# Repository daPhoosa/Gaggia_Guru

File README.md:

# Gaggia Guru

ESP32-WROOM-32U control system for a converted Gaggia Classic Pro espresso machine.
PlatformIO / Arduino firmware with:

- **Wi-Fi manager** – joins a saved network; if none or it fails, starts a setup AP
  (`GaggiaGuru-Setup-XXXXXX`) with a captive portal so you can enter credentials from a phone.
  Credentials are kept in NVS and survive firmware updates.
- **OTA updates, two ways**
  - **ArduinoOTA / espota** – `pio run -e esp32-ota -t upload` from your PC.
  - **Browser upload** – Update tab on the dashboard, or the always-available
    fallback page at `/update` (works even if the filesystem is empty).
- **Async web server** serving a dashboard from LittleFS (`data/`) with live status
  over WebSocket (uptime, heap, RSSI, flash/FS usage, boot partition…).
- **mDNS** – `http://gaggia-guru.local`

> The **-32U** has no PCB antenna — connect an external 2.4 GHz antenna to the u.FL
> connector before powering up Wi-Fi.

## Layout

```
IO_design.md          pin assignments, wiring and signal conditioning (hardware reference)
docs/design_guide.md  dashboard color & design guide (live: follow it for every UI change, keep it updated)
PCB/                  KiCad 10 carrier-board schematic, project symbols and ESP32U footprint
PCB/RelayBoard/       KiCad 10 relay board (lamp relays + valve SSR), shares the PCB/ libraries
platformio.ini        build envs: esp32-serial (USB), esp32-ota (Wi-Fi), native (tests)
partitions.csv        4MB: 2 × 1.5MB OTA app slots, 896KB LittleFS, coredump
include/secrets.h     passwords, optional Wi-Fi creds (git-ignored; copy from secrets.example.h)  ← edit first
include/config.h      hostname, AP name, ports, timings
include/machine_config.h  setpoint/PID defaults, safety limits, control timing
include/io_pins.h     every GPIO: '#define PIN_X n // Name | Type | notes'
scripts/gen_io_pins.py  pre-build: io_pins.h comments → include/io_pins_table.gen.h
scripts/ota_auth.py   esp32-ota upload: takes the OTA password from secrets.h
src/main.cpp          setup/loop; loads forced OFF first, machine control started before Wi-Fi
src/machine.*         control task (own FreeRTOS task + watchdog): pin I/O, logging, status publishing
src/machine_logic.*   state machine, heater/pump PID, safety faults (hardware-free, unit-tested)
src/sensors.*         MAX31855K thermocouple, XDB401 pressure sensor via ADS1115 (pin / I2C I/O)
src/sensor_math.*     MAX31855 frame decoding, voltage -> bar (hardware-free, unit-tested)
src/pump.*            RobotDyn dimmer: zero-cross ISR, full-cycle pulse-skip modulation
src/settings.*        user settings (setpoints, PID gains) in NVS
src/settings_schema.* settings field table, defaults, range checks (hardware-free, unit-tested)
src/pid.h             PID controller
src/wifi_manager.*    STA connect, fallback AP, captive DNS, scan, NVS creds
src/ota.*             ArduinoOTA
src/web_server.*      HTTP routes, JSON API, WebSocket, browser OTA
src/io_status.*       read-only pin sampling for /api/io
src/cpu_load.*        per-core CPU load estimate (idle-task loop counting) for the Device status card
test/                 PC unit tests (pio test -e native), see test/README.md
data/                 web UI → LittleFS: index.html (dashboard), settings.html, wifi.html, test.html,
                      update.html, io.html, shared style.css + app.js, fonts/Inter.woff2
                      (styled per docs/design_guide.md)
```

## First flash (USB)

1. Create your secrets file and set real passwords in it (`OTA_PASSWORD`, `ADMIN_PASSWORD`,
   `AP_PASSWORD`, optionally `DEFAULT_WIFI_SSID` / `DEFAULT_WIFI_PASS`):
   ```sh
   cp include/secrets.example.h include/secrets.h
   ```
   `include/secrets.h` is git-ignored; the build stops with an error if it is missing.
   The Wi-Fi upload reads `OTA_PASSWORD` from it, so there is nothing to keep in sync.
2. Flash firmware and the dashboard filesystem:
   ```sh
   pio run -e esp32-serial -t upload
   pio run -e esp32-serial -t uploadfs
   pio device monitor
   ```
3. If no Wi-Fi is configured, join `GaggiaGuru-Setup-XXXXXX` (password `AP_PASSWORD`),
   browse to `http://192.168.4.1`, open **Wi-Fi**, pick a network, Save. The device reboots
   onto your network.

## Unit tests (PC, no hardware)

```sh
pio test -e native
```
Runs on the PC with the host compiler (g++ or clang). Covers the control logic and every
software safety fault, sensor decoding, settings validation and the PID. See
[test/README.md](test/README.md). Run it after changing anything in `machine_logic`,
`sensor_math`, `settings_schema` or `pid.h`.

## Updating over Wi-Fi

```sh
pio run -e esp32-ota -t upload      # firmware
pio run -e esp32-ota -t uploadfs    # dashboard files
```
If `gaggia-guru.local` doesn't resolve, set `upload_port` in `platformio.ini` to the IP.
The OTA password comes from `OTA_PASSWORD` in `include/secrets.h`; the environment variable
`GAGGIA_OTA_PASS` overrides it (e.g. when the device still has an older password).

If a filesystem upload fails part-way, the device mounts LittleFS again. If the partition was
already partly overwritten, `/` serves the built-in Wi-Fi setup page instead of the dashboard;
use its **Firmware update** link (or `uploadfs`) to upload `littlefs.bin` again.

Or from the browser: **Update** tab → choose `.pio/build/esp32-serial/firmware.bin`
(or `littlefs.bin` from `pio run -t buildfs`) → Upload. Login is `ADMIN_USER` / `ADMIN_PASSWORD`.

Bump `-DFW_VERSION` in `platformio.ini` to see the new version on the dashboard.

## HTTP API

| Method | Path                           | Auth*  | Description                          |
|--------|--------------------------------|--------|--------------------------------------|
| GET    | `/api/status`                  | –      | Device status JSON (incl. CPU load estimate, control tick timing) |
| WS     | `/ws`                          | –      | Status JSON pushed every 2 s         |
| GET    | `/api/machine`                 | –      | Machine state, temperature, pressure, outputs, fault |
| WS     | `/ws` (`"type":"machine"`)     | –      | Machine JSON pushed every 0.5 s      |
| GET    | `/api/settings`                | –      | Settings values, defaults and limits |
| POST   | `/api/settings` (any of the setting keys) | admin | Validate, apply and save settings |
| POST   | `/api/settings/reset`          | admin  | Restore default settings             |
| GET    | `/api/io`                      | –      | Pin names/types (from io_pins.h) + live state |
| GET    | `/test.html` (or `/test`)      | admin  | Output test page (manual heater / pump / valve / lights) |
| POST   | `/api/test` (`action=start`, `update`, `stop`) | admin | Start, drive (and keep alive) or stop the output test |
| GET    | `/api/wifi/scan`               | –      | Nearby networks (async; poll)        |
| POST   | `/api/wifi` (`ssid`, `pass`)   | admin† | Save credentials and reboot          |
| POST   | `/api/wifi/forget`             | admin  | Clear credentials and reboot         |
| POST   | `/api/reboot`                  | admin  | Reboot                               |
| POST   | `/api/update?target=firmware\|fs` | admin | Multipart `.bin` upload (one file), reboots on success; `409` while another update (browser or ArduinoOTA) is running |
| GET    | `/update`                      | admin  | Minimal fallback upload page         |

\* HTTP Basic auth. † Open while in setup-AP mode so first-time provisioning works.

Every POST must also carry the header `X-Guru: 1`, or an `Origin` header equal to the
device's own address; anything else gets `403`. This stops other web pages open in the
same browser from changing settings (cross-site request forgery). The dashboard pages add the
header automatically. The address used must also be one of the device's own names: its IP
address, `gaggia-guru`, or `gaggia-guru` followed by `.local`, `.lan`, `.home`, `.home.arpa`,
`.localdomain` or `.internal`. This blocks DNS rebinding, where another website's name is
pointed at the machine. POSTs sent to any other name, including through a reverse proxy, get
`403`. From a script:

```sh
curl -u admin:PASSWORD -H 'X-Guru: 1' -d coffeeTempC=93 http://gaggia-guru.local/api/settings
```

The server sends no CORS headers, so other sites can't read the API either.

## IO pin map

`include/io_pins.h` lists every usable GPIO of the ESP32-WROOM-32U in 38-pin board order.
Each active line must be:

```c
#define PIN_RELAY_1   4   // RELAY_1 | Digital | drives K1 via Q1
```

- **Type** is one of `Analog`, `Digital`, `Communications`, `Unused`.
- Lines starting with `//` are ignored (flash pins GPIO6–11, and GPIO37/38 which the module lacks).
- `scripts/gen_io_pins.py` parses the comments on every build and fails the build with a
  clear message on a bad type, duplicate GPIO, flash pin or missing comment.
- The dashboard's **IO Status** page shows each pin's name, type, mode (IN/OUT/PERIPH/ANALOG),
  pull-up/down and level (HIGH/LOW), refreshed every second. Reading is non-invasive and the
  page never touches the ADC. Brew pressure is read by the ADS1115 over I²C, so it is shown
  on the dashboard, not here.
  ADC2 pins can't be read while Wi-Fi is on — use ADC1 (GPIO32–39) for analog inputs.

## Machine operation

| Coffee | Steam | State       | Boiler target (thermocouple) | Pump        | Valve  |
|--------|-------|-------------|------------------------------|-------------|--------|
| off    | off   | `IDLE`      | coffee + offset (93 + 7 = 100 °C) | off    | closed |
| on     | off   | `BREWING`   | coffee + offset              | PID to brew pressure (6 bar) | open |
| off    | on    | `STEAM`     | steam (145 °C)               | off         | closed |
| on     | on    | `HOT_WATER` | steam                        | 100 %       | closed |

- **Output test (`TEST`):** the admin-only **Output test** page (linked from IO Status)
  switches the heater, pump (with a duty cycle, default 100 %), valve and both lights by
  hand, and shows the switches, thermocouple, pressure and mains frequency. It starts only
  from `IDLE` with both switches off and ends on Stop, either switch turning on, a fault, a
  firmware update, or 5 s without a keep-alive from the page (it sends one every second;
  closing the page stops it at once). All safety faults stay active; the manual heater is
  held off above 150 °C (2 °C hysteresis) and the pump stops after 120 s until toggled off
  and on. Leaving the test with the Coffee switch on does not start a shot: it must be cycled.
- **Brew Temp Offset** (default 7 °C, range -10 to 20 °C): how much hotter the boiler
  thermocouple reads than the water at the portafilter. The Coffee setting (default 93 °C) is
  the water temperature; in coffee mode the heater PID aims for Coffee + offset and the
  dashboard shows thermocouple − offset, so the reading compares directly with the target.
  While brewing, the PID aims `BREW_TEMP_BIAS_C` (1 °C, machine_config.h) higher still to
  make up for the incoming cold water; the shown target and ready light don't change.
  Steam and hot water ignore the offset. Safety checks always use the thermocouple; the
  dashboard's Thermocouple row shows the raw reading and target.

- **Lights:** the active mode's light comes on once the temperature is within ± the **Ready
  band** of its target, then stays on (overshoot included) until it drops more than the band
  below the target (setting, default 3 °C, range 0.5 to 10 °C; one band for both lights).
  Switching from steam to coffee, the Coffee light waits for the boiler to cool into the band.
  Both blink on a fault.
- **Coffee switch arming:** if the Coffee switch is on at power-up (or after an update),
  it is ignored until turned off and on again. The pump also stops after 120 s of
  continuous running and needs the same off/on cycle.
- **Faults** (latched until power cycle, everything off): thermocouple fault, boiler
  above 155 °C, boiler not heating at full power for 120 s (high-limit tripped, fuse,
  element or loose probe), no zero-cross signal while pumping, pressure sensor out of
  range while brewing. The dashboard shows the cause.
- Firmware updates and reboots switch all loads off first.
- Settings (temperatures, pressure, PID gains) are on the dashboard **Settings** page.

## Adding your own features

- Machine behaviour lives in `src/machine.cpp` (`tick()` runs every 50 ms).
- Add fields to `statusJson()` in `src/web_server.cpp` and render them in `data/app.js`
  — they're pushed to the dashboard automatically.
- Add routes in `WebUi::begin()`.

## Notes

- Basic auth over plain HTTP is not encrypted; keep the device on a trusted network.
- `STATUS_LED_PIN` defaults to GPIO2 (common on dev boards); set `-1` if your board differs.
- Flash size: WROOM-32U modules come in 4/8/16MB. This project assumes 4MB; for larger
  modules, change `board_build.flash_size` and enlarge the partitions.

## Troubleshooting

- **Android Chrome can't open the dashboard (Firefox can):** newer Android versions require apps
  to have permission to reach local-network devices. Settings → Apps → Chrome → Permissions →
  **Nearby devices** (a.k.a. *Local network*) → Allow.
- **`pio run -e esp32-ota -t upload` stops at "No response from device":** the ESP32 connects
  back to the PC on a TCP host port (3233–3240, picked per upload by `scripts/espota_port.py`). Allow the range in the PC firewall, e.g.
  `sudo ufw allow from 192.168.1.0/24 to any port 3233:3240 proto tcp`.

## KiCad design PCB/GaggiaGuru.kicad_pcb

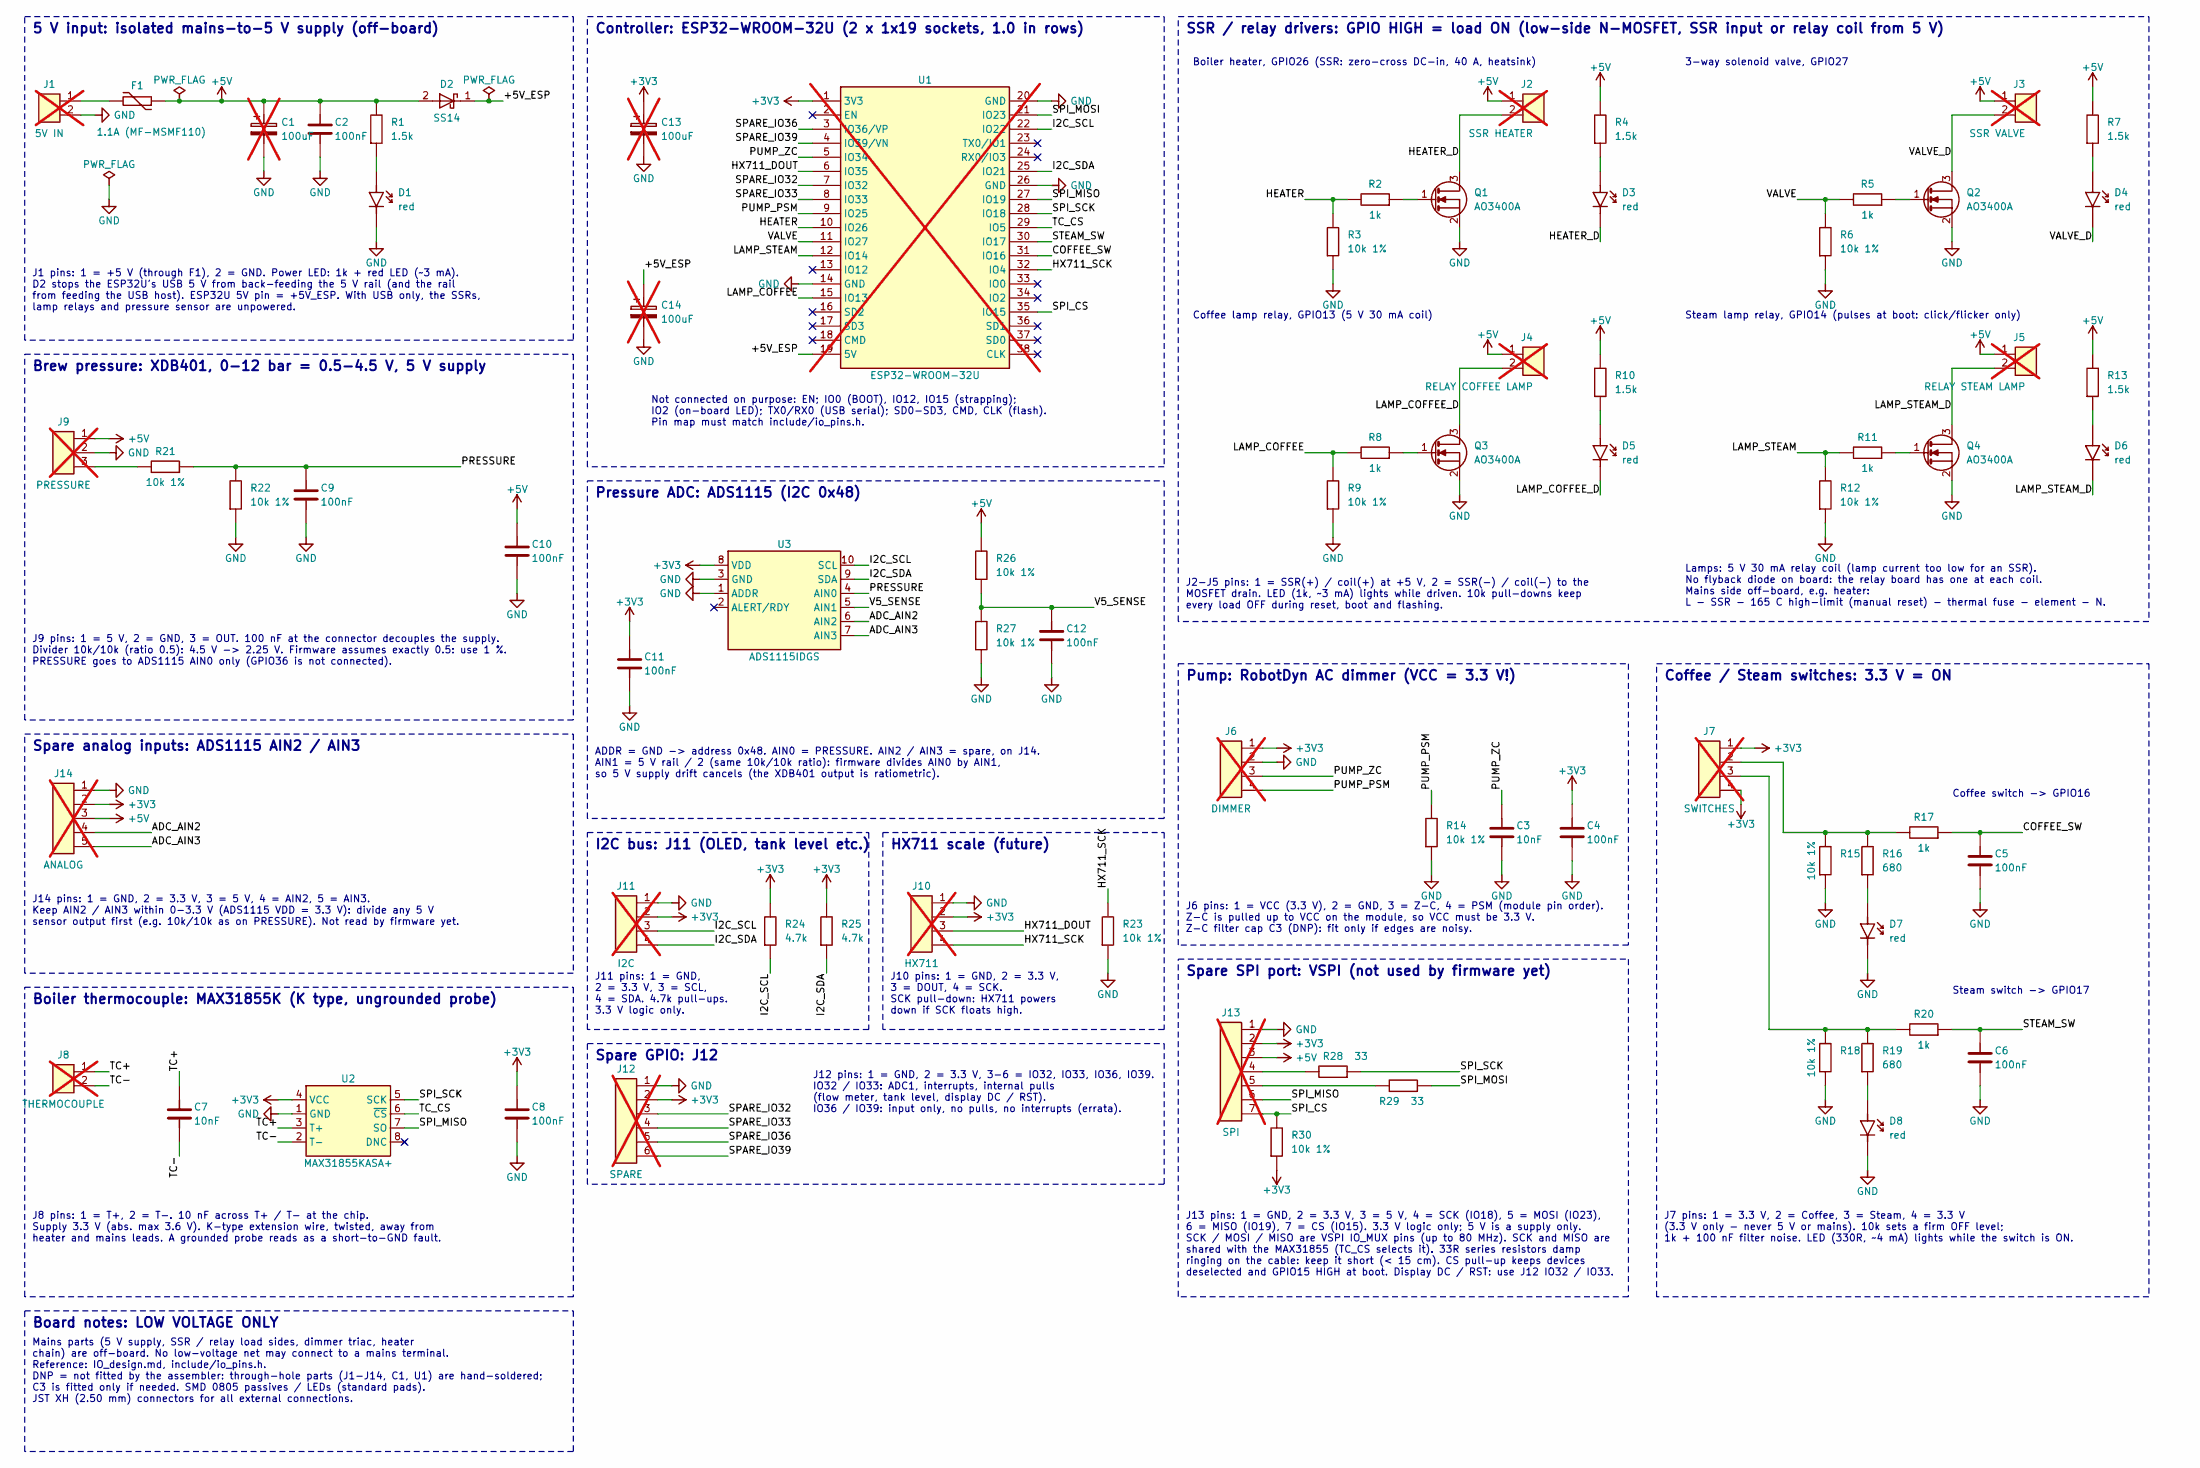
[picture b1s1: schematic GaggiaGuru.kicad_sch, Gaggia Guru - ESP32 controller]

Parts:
C1, C13, C14: 100uF; CP_Radial_D6.3mm_P2.50mm; Rating 10 V min, low ESR, radial THT; not fitted
C2, C4, C5, C6, C8, C9, C10, C11, C12: 100nF; C_0805_2012Metric
C3, C7: 10nF; C_0805_2012Metric
D1, D3, D4, D5, D6, D7, D8: red; LED_0805_2012Metric
D2: SS14; D_SMA
F1: 1.1A (MF-MSMF110); Fuse_1812_4532Metric
J1: 5V IN; JST_XH_B2B-XH-A_1x02_P2.50mm_Vertical; not fitted
J2: SSR HEATER; JST_XH_B2B-XH-A_1x02_P2.50mm_Vertical; not fitted
J3: SSR VALVE; JST_XH_B2B-XH-A_1x02_P2.50mm_Vertical; not fitted
J4: RELAY COFFEE LAMP; JST_XH_B2B-XH-A_1x02_P2.50mm_Vertical; not fitted
J5: RELAY STEAM LAMP; JST_XH_B2B-XH-A_1x02_P2.50mm_Vertical; not fitted
J6: DIMMER; JST_XH_B4B-XH-A_1x04_P2.50mm_Vertical; not fitted
J7: SWITCHES; JST_XH_B4B-XH-A_1x04_P2.50mm_Vertical; not fitted
J8: THERMOCOUPLE; JST_XH_B2B-XH-A_1x02_P2.50mm_Vertical; not fitted
J9: PRESSURE; JST_XH_B3B-XH-A_1x03_P2.50mm_Vertical; not fitted
J10: HX711; JST_XH_B4B-XH-A_1x04_P2.50mm_Vertical; not fitted
J11: I2C; JST_XH_B4B-XH-A_1x04_P2.50mm_Vertical; not fitted
J12: SPARE; JST_XH_B6B-XH-A_1x06_P2.50mm_Vertical; not fitted
J13: SPI; JST_XH_B7B-XH-A_1x07_P2.50mm_Vertical; not fitted
J14: ANALOG; JST_XH_B5B-XH-A_1x05_P2.50mm_Vertical; not fitted
Q1, Q2, Q3, Q4: AO3400A; SOT-23
R1, R4, R7, R10, R13: 1.5k; R_0805_2012Metric
R2, R5, R8, R11, R17, R20: 1k; R_0805_2012Metric
R3, R6, R9, R12, R14, R15, R18, R21, R22, R23, R26, R27, R30: 10k 1%; R_0805_2012Metric
R16, R19: 680; R_0805_2012Metric
R24, R25: 4.7k; R_0805_2012Metric
R28, R29: 33; R_0805_2012Metric
U1: ESP32-WROOM-32U; ESP32U-38_P25.4mm; not fitted
U2: MAX31855KASA+; SOIC-8_3.9x4.9mm_P1.27mm
U3: ADS1115IDGS; TSSOP-10_3x3mm_P0.5mm

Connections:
+3V3: C4.1, C8.1, C11.1, C13.1, J6.1, J7.1, J7.4, J10.2, J11.2, J12.2, J13.2, J14.2, R24.1, R25.1, R30.2, U1.1 (3V3), U2.4 (VCC), U3.8 (VDD)
+5V: C1.1, C2.1, C10.1, D2.2 (A), F1.2, J2.1, J3.1, J4.1, J5.1, J9.1, J13.3, J14.3, R1.1, R4.1, R7.1, R10.1, R13.1, R26.1
/+5V_ESP: C14.1, D2.1 (K), U1.19 (5V)
/ADC_AIN2: J14.4, U3.6 (AIN2)
/ADC_AIN3: J14.5, U3.7 (AIN3)
/COFFEE_SW: C5.1, R17.2, U1.31 (IO16)
/HEATER: R2.1, R3.1, U1.10 (IO26)
/HEATER_D: D3.1 (K), J2.2, Q1.3 (D)
/HX711_DOUT: J10.3, U1.6 (IO35)
/HX711_SCK: J10.4, R23.1, U1.32 (IO4)
/I2C_SCL: J11.3, R24.2, U1.22 (IO22), U3.10 (SCL)
/I2C_SDA: J11.4, R25.2, U1.25 (IO21), U3.9 (SDA)
/LAMP_COFFEE: R8.1, R9.1, U1.15 (IO13)
/LAMP_COFFEE_D: D5.1 (K), J4.2, Q3.3 (D)
/LAMP_STEAM: R11.1, R12.1, U1.12 (IO14)
/LAMP_STEAM_D: D6.1 (K), J5.2, Q4.3 (D)
/PRESSURE: C9.1, R21.2, R22.1, U3.4 (AIN0)
/PUMP_PSM: J6.4, R14.1, U1.9 (IO25)
/PUMP_ZC: C3.1, J6.3, U1.5 (IO34)
/SPARE_IO32: J12.3, U1.7 (IO32)
/SPARE_IO33: J12.4, U1.8 (IO33)
/SPARE_IO36: J12.5, U1.3 (IO36/VP)
/SPARE_IO39: J12.6, U1.4 (IO39/VN)
/SPI_CS: J13.7, R30.1, U1.35 (IO15)
/SPI_MISO: J13.6, U1.27 (IO19), U2.7 (SO)
/SPI_MOSI: R29.2, U1.21 (IO23)
/SPI_SCK: R28.2, U1.28 (IO18), U2.5 (SCK)
/STEAM_SW: C6.1, R20.2, U1.30 (IO17)
/TC+: C7.1, J8.1, U2.3 (T+)
/TC-: C7.2, J8.2, U2.2 (T-)
/TC_CS: U1.29 (IO5), U2.6 (~CS)
/V5_SENSE: C12.1, R26.2, R27.1, U3.5 (AIN1)
/VALVE: R5.1, R6.1, U1.11 (IO27)
/VALVE_D: D4.1 (K), J3.2, Q2.3 (D)
GND: C1.2, C2.2, C3.2, C4.2, C5.2, C6.2, C8.2, C9.2, C10.2, C11.2, C12.2, C13.2, C14.2, D1.1 (K), D7.1 (K), D8.1 (K), J1.2, J6.2, J9.2, J10.1, J11.1, J12.1, J13.1, J14.1, Q1.2 (S), Q2.2 (S), Q3.2 (S), Q4.2 (S), R3.2, R6.2, R9.2, R12.2, R14.2, R15.2, R18.2, R22.2, R23.2, R27.2, U1.14 (GND), U1.20 (GND), U1.26 (GND), U2.1 (GND), U3.1 (ADDR), U3.3 (GND)
unnamed: D1.2 (A), R1.2
unnamed: D3.2 (A), R4.2
unnamed: D4.2 (A), R7.2
unnamed: D5.2 (A), R10.2
unnamed: D6.2 (A), R13.2
unnamed: D7.2 (A), R16.2
unnamed: D8.2 (A), R19.2
unnamed: F1.1, J1.1
unnamed: J7.2, R15.1, R16.1, R17.1
unnamed: J7.3, R18.1, R19.1, R20.1
unnamed: J9.3, R21.1
unnamed: J13.4, R28.1
unnamed: J13.5, R29.1
unnamed: Q1.1 (G), R2.2
unnamed: Q2.1 (G), R5.2
unnamed: Q3.1 (G), R8.2
unnamed: Q4.1 (G), R11.2

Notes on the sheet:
Coffee / Steam switches: 3.3 V = ON
Lamps: 5 V 30 mA relay coil (lamp current too low for an SSR). No flyback diode on board: the relay board has one at each coil. Mains side off-board, e.g. heater: L - SSR - 165 C high-limit (manual reset) - thermal fuse - element - N.
Boiler thermocouple: MAX31855K (K type, ungrounded probe)
I2C bus: J11 (OLED, tank level etc.)
J12 pins: 1 = GND, 2 = 3.3 V, 3-6 = IO32, IO33, IO36, IO39. IO32 / IO33: ADC1, interrupts, internal pulls (flow meter, tank level, display DC / RST). IO36 / IO39: input only, no pulls, no interrupts (errata).
ADDR = GND -> address 0x48. AIN0 = PRESSURE. AIN2 / AIN3 = spare, on J14. AIN1 = 5 V rail / 2 (same 10k/10k ratio): firmware divides AIN0 by AIN1, so 5 V supply drift cancels (the XDB401 output is ratiometric).
Mains parts (5 V supply, SSR / relay load sides, dimmer triac, heater chain) are off-board. No low-voltage net may connect to a mains terminal. Reference: IO_design.md, include/io_pins.h. DNP = not fitted by the assembler: through-hole parts (J1-J14, C1, U1) are hand-soldered; C3 is fitted only if 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
Spare GPIO: J12
HX711 scale (future)
Pressure ADC: ADS1115 (I2C 0x48)
Steam switch -> GPIO17
Boiler heater, GPIO26 (SSR: zero-cross DC-in, 40 A, heatsink)
Steam lamp relay, GPIO14 (pulses at boot: click/flicker only)
Spare analog inputs: ADS1115 AIN2 / AIN3
3-way solenoid valve, GPIO27
Controller: ESP32-WROOM-32U (2 x 1x19 sockets, 1.0 in rows)
J14 pins: 1 = GND, 2 = 3.3 V, 3 = 5 V, 4 = AIN2, 5 = AIN3. Keep AIN2 / AIN3 within 0-3.3 V (ADS1115 VDD = 3.3 V): divide any 5 V sensor output first (e.g. 10k/10k as on PRESSURE). Not read by firmware yet.
J7 pins: 1 = 3.3 V, 2 = Coffee, 3 = Steam, 4 = 3.3 V (3.3 V only - never 5 V or mains). 10k sets a firm OFF level; 1k + 100 nF filter noise. LED (330R, ~4 mA) lights while the switch is ON.
Board notes: LOW VOLTAGE ONLY
J10 pins: 1 = GND, 2 = 3.3 V, 3 = DOUT, 4 = SCK. SCK pull-down: HX711 powers down if SCK floats high.
Coffee lamp relay, GPIO13 (5 V 30 mA coil)
J9 pins: 1 = 5 V, 2 = GND, 3 = OUT. 100 nF at the connector decouples the supply. Divider 10k/10k (ratio 0.5): 4.5 V -> 2.25 V. Firmware assumes exactly 0.5: use 1 %. PRESSURE goes to ADS1115 AIN0 only (GPIO36 is not connected).
Coffee switch -> GPIO16
J8 pins: 1 = T+, 2 = T-. 10 nF across T+ / T- at the chip. Supply 3.3 V (abs. max 3.6 V). K-type extension wire, twisted, away from heater and mains leads. A grounded probe reads as a short-to-GND fault.
J11 pins: 1 = GND, 2 = 3.3 V, 3 = SCL, 4 = SDA. 4.7k pull-ups. 3.3 V logic only.
J2-J5 pins: 1 = SSR(+) / coil(+) at +5 V, 2 = SSR(-) / coil(-) to the MOSFET drain. LED (1k, ~3 mA) lights while driven. 10k pull-downs keep every load OFF during reset, boot and flashing.
J6 pins: 1 = VCC (3.3 V), 2 = GND, 3 = Z-C, 4 = PSM (module pin order). Z-C is pulled up to VCC on the module, so VCC must be 3.3 V. Z-C filter cap C3 (DNP): fit only if edges are noisy.
Not connected on purpose: EN; IO0 (BOOT), IO12, IO15 (strapping); IO2 (on-board LED); TX0/RX0 (USB serial); SD0-SD3, CMD, CLK (flash). Pin map must match include/io_pins.h.
Spare SPI port: VSPI (not used by firmware yet)
Brew pressure: XDB401, 0-12 bar = 0.5-4.5 V, 5 V supply
J1 pins: 1 = +5 V (through F1), 2 = GND. Power LED: 1k + red LED (~3 mA). D2 stops the ESP32U's USB 5 V from back-feeding the 5 V rail (and the rail from feeding the USB host). ESP32U 5V pin = +5V_ESP. With USB only, the SSRs, lamp relays and pressure sensor are unpowered.
J13 pins: 1 = GND, 2 = 3.3 V, 3 = 5 V, 4 = SCK (IO18), 5 = MOSI (IO23), 6 = MISO (IO19), 7 = CS (IO15). 3.3 V logic only; 5 V is a supply only. SCK / MOSI / MISO are VSPI IO_MUX pins (up to 80 MHz). SCK and MISO are shared with the MAX31855 (TC_CS selects it). 33R series resistors damp ringing on t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
SSR / relay drivers: GPIO HIGH = load ON (low-side N-MOSFET, SSR input or relay coil from 5 V)
Pump: RobotDyn AC dimmer (VCC = 3.3 V!)
5 V input: isolated mains-to-5 V supply (off-board)

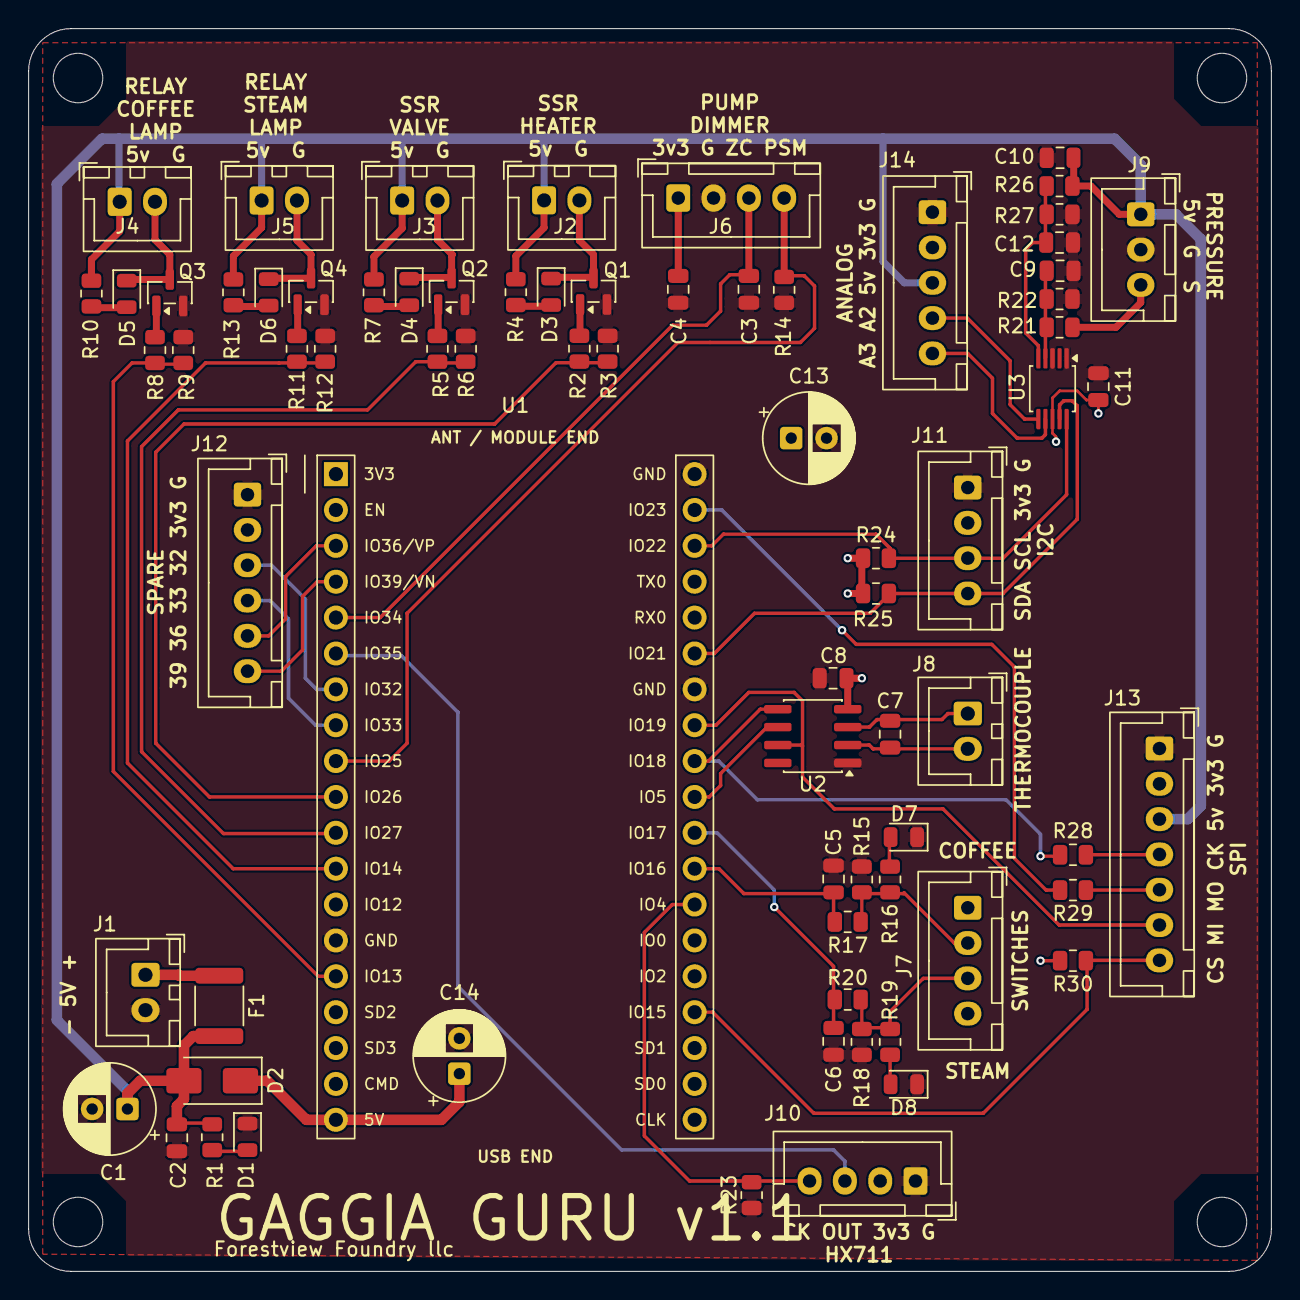
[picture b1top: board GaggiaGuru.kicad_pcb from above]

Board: 2 copper layers, 88.0 x 88.0 mm, 74 parts (0 on the bottom side), 52 nets.

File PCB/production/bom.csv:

Designator,Footprint,Quantity,Value,LCSC Part #
C1,CP_Radial_D6.3mm_P2.50mm,1,100uF,
"C10, C11, C12, C2, C4, C5, C6, C8, C9",0805,9,100nF,
"C3, C7",0805,2,10nF,
"D1, D3, D4, D5, D6, D7, D8",0805,7,red,
D2,D_SMA,1,SS14,
F1,1812,1,1.1A (MF-MSMF110),
J1,JST_XH_B2B-XH-A_1x02_P2.50mm_Vertical,1,5V IN,
J10,JST_XH_B4B-XH-A_1x04_P2.50mm_Vertical,1,HX711,
J11,JST_XH_B4B-XH-A_1x04_P2.50mm_Vertical,1,I2C,
J12,JST_XH_B6B-XH-A_1x06_P2.50mm_Vertical,1,SPARE,
J13,JST_XH_B7B-XH-A_1x07_P2.50mm_Vertical,1,SPI,
J14,JST_XH_B5B-XH-A_1x05_P2.50mm_Vertical,1,ANALOG,
J2,JST_XH_B2B-XH-A_1x02_P2.50mm_Vertical,1,SSR HEATER,
J3,JST_XH_B2B-XH-A_1x02_P2.50mm_Vertical,1,SSR VALVE,
J4,JST_XH_B2B-XH-A_1x02_P2.50mm_Vertical,1,RELAY COFFEE LAMP,
J5,JST_XH_B2B-XH-A_1x02_P2.50mm_Vertical,1,RELAY STEAM LAMP,
J6,JST_XH_B4B-XH-A_1x04_P2.50mm_Vertical,1,DIMMER,
J7,JST_XH_B4B-XH-A_1x04_P2.50mm_Vertical,1,SWITCHES,
J8,JST_XH_B2B-XH-A_1x02_P2.50mm_Vertical,1,THERMOCOUPLE,
J9,JST_XH_B3B-XH-A_1x03_P2.50mm_Vertical,1,PRESSURE,
"Q1, Q2, Q3, Q4",SOT-23,4,AO3400A,
"R1, R10, R11, R13, R17, R2, R20, R4, R5, R7, R8",0805,11,1k,
"R12, R14, R15, R18, R21, R22, R23, R26, R27, R3, R30, R6, R9",0805,13,10k 1%,
"R16, R19",0805,2,330,
"R24, R25",0805,2,4.7k,
"R28, R29",0805,2,33,
U1,ESP32U-38_P25.4mm,1,ESP32-WROOM-32U,
U2,SOIC-8_3.9x4.9mm_P1.27mm,1,MAX31855KASA+,
U3,TSSOP-10_3x3mm_P0.5mm,1,ADS1115IDGS,

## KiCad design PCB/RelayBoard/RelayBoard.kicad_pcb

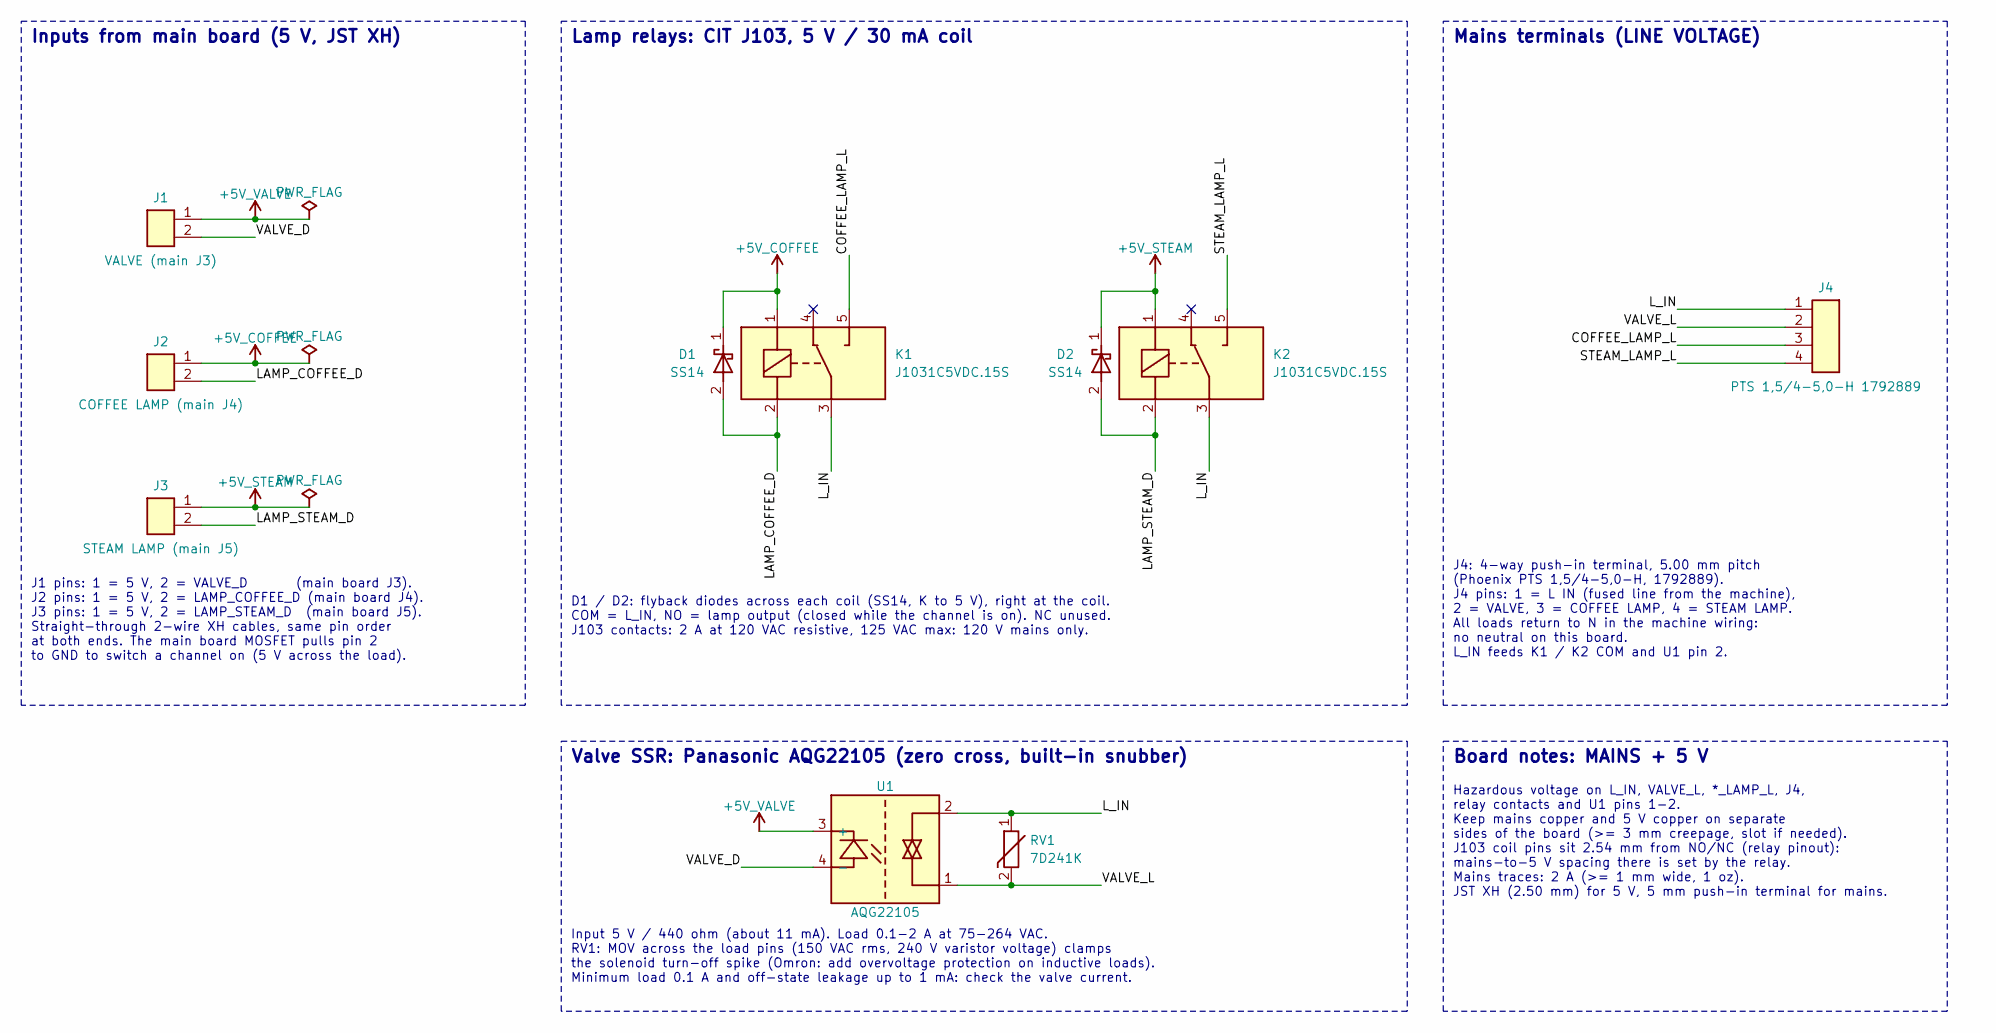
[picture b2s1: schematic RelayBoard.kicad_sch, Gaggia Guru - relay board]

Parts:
D1, D2: SS14; D_SMA
J1: VALVE (main J3); JST_XH_B2B-XH-A_1x02_P2.50mm_Vertical
J2: COFFEE LAMP (main J4); JST_XH_B2B-XH-A_1x02_P2.50mm_Vertical
J3: STEAM LAMP (main J5); JST_XH_B2B-XH-A_1x02_P2.50mm_Vertical
J4: PTS 1,5/4-5,0-H 1792889; TerminalBlock_Phoenix_MKDS-1,5-4_1x04_P5.00mm_Horizontal; MPN 1792889
K1, K2: J1031C5VDC.15S; Relay_SPDT_CIT_J103
RV1: 7D241K; RV_Disc_D7mm_W3.4mm_P5mm
U1: AQG22105; SSR_Panasonic_AQG22

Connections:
+5V_COFFEE: D1.1 (K), J2.1, K1.1
+5V_STEAM: D2.1 (K), J3.1, K2.1
+5V_VALVE: J1.1, U1.3 (+)
/COFFEE_LAMP_L: J4.3, K1.5 (NO)
/LAMP_COFFEE_D: D1.2 (A), J2.2, K1.2
/LAMP_STEAM_D: D2.2 (A), J3.2, K2.2
/L_IN: J4.1, K1.3 (COM), K2.3 (COM), RV1.1, U1.2
/STEAM_LAMP_L: J4.4, K2.5 (NO)
/VALVE_D: J1.2, U1.4 (-)
/VALVE_L: J4.2, RV1.2, U1.1

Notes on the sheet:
Mains terminals (LINE VOLTAGE)
Board notes: MAINS + 5 V
J4: 4-way push-in terminal, 5.00 mm pitch (Phoenix PTS 1,5/4-5,0-H, 1792889). J4 pins: 1 = L IN (fused line from the machine), 2 = VALVE, 3 = COFFEE LAMP, 4 = STEAM LAMP. All loads return to N in the machine wiring: no neutral on this board. L_IN feeds K1 / K2 COM and U1 pin 2.
D1 / D2: flyback diodes across each coil (SS14, K to 5 V), right at the coil. COM = L_IN, NO = lamp output (closed while the channel is on). NC unused. J103 contacts: 2 A at 120 VAC resistive, 125 VAC max: 120 V mains only.
Valve SSR: Panasonic AQG22105 (zero cross, built-in snubber)
Lamp relays: CIT J103, 5 V / 30 mA coil
Hazardous voltage on L_IN, VALVE_L, *_LAMP_L, J4, relay contacts and U1 pins 1-2. Keep mains copper and 5 V copper on separate sides of the board (>= 3 mm creepage, slot if needed). J103 coil pins sit 2.54 mm from NO/NC (relay pinout): mains-to-5 V spacing there is set by the relay. Mains traces: 2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
Inputs from main board (5 V, JST XH)
J1 pins: 1 = 5 V, 2 = VALVE_D (main board J3). J2 pins: 1 = 5 V, 2 = LAMP_COFFEE_D (main board J4). J3 pins: 1 = 5 V, 2 = LAMP_STEAM_D (main board J5). Straight-through 2-wire XH cables, same pin order at both ends. The main board MOSFET pulls pin 2 to GND to switch a channel on (5 V across the loa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
Input 5 V / 440 ohm (about 11 mA). Load 0.1-2 A at 75-264 VAC. RV1: MOV across the load pins (150 VAC rms, 240 V varistor voltage) clamps the solenoid turn-off spike (Omron: add overvoltage protection on inductive loads). Minimum load 0.1 A and off-state leakage up to 1 mA: check the valve current.

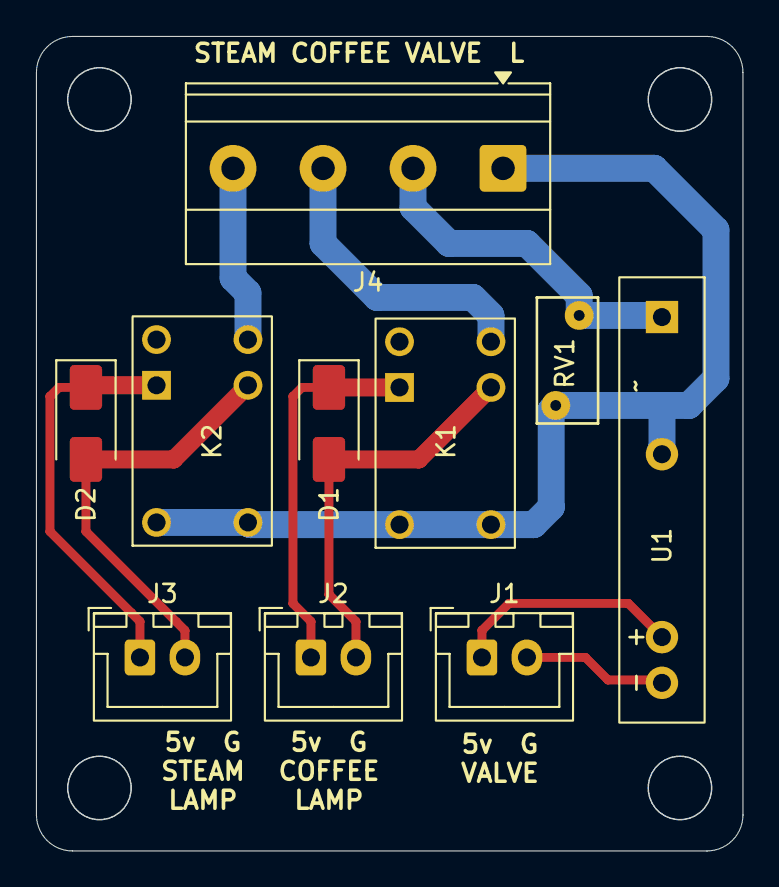
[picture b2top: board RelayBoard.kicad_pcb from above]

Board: 2 copper layers, 39.2 x 45.2 mm, 10 parts (0 on the bottom side), 10 nets.

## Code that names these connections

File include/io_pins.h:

#pragma once
// ===========================================================================
// Gaggia Guru - ESP32-WROOM-32U hardware IO pin map (38-pin ESP32U board)
// ===========================================================================
//
// EVERY ACTIVE PIN LINE MUST FOLLOW THIS FORMAT (parsed at build time by
// scripts/gen_io_pins.py to build the dashboard's "IO Status" page):
//
//   #define <MACRO>  <gpio>   // <Name> | <Type> | <optional notes>
//
//   Name   Label shown on the IO Status page (no '|' characters).
//   Type   One of: Analog, Digital, Communications, Unused
//   Notes  Free text: board label, restrictions, what's connected, ...
//
// Lines that start with "//" are ignored (pins not on a typical 38-pin board,
// or not usable). Each GPIO number may be active only once.
//
// Machine: Gaggia Classic Pro, 120 V / 60 Hz. Stock thermostats removed.
// Heater chain: SSR -> 165 C manual-reset high-limit thermostat -> thermal fuse -> element.
//
// Hardware rules for this build
//   - Heater/valve drive SSRs; the coffee/steam lamps drive external 5 V
//     electromechanical relays (~30 mA coil) - lamps draw too little for an SSR.
//   - Every SSR / relay / dimmer drive pin has an external 10k pull-down so loads stay
//     OFF while the ESP32 is in reset, booting or being flashed.
//   - Coffee/Steam switches feed 3.3 V (never 5 V). Internal pull-down is
//     enabled in firmware; add external 10k pull-down + 100 nF for noise.
//   - RobotDyn dimmer VCC = 3.3 V (its Z-C output is pulled up to VCC).
//   - MAX31855K board VCC = 3.3 V (chip max 3.6 V). Conversion ~100 ms (<= 10 Hz).
//     Thermocouple MUST be ungrounded/insulated junction: a probe touching the
//     earthed boiler makes the MAX31855 report a short-to-GND fault.
//   - XDB401 pressure sensor: 5 V supply, 0.5-4.5 V out through a 10k/10k
//     divider into the ADS1115 (I2C), not an ESP32 pin. GPIO36 is not connected.
//
// Quick reference
//   Input only, no internal pull-ups/downs : GPIO34, 35, 36 (VP), 39 (VN)
//   Strapping pins (level at reset matters): GPIO0, 2, 5, 12, 15
//   ADC1 (usable with Wi-Fi on)            : GPIO32-39
//   ADC2 (NOT usable while Wi-Fi is on)    : GPIO0, 2, 4, 12-15, 25-27
//   GPIO36/39 can raise false interrupts while the ADC is active: no ISRs there.
// ===========================================================================

// ---- Left header (top to bottom, antenna end up): 3V3, EN, then ------------
#define PIN_GPIO36        36  // GPIO36 | Unused | Spare (J12). Board VP. Input only, no pull-ups. ADC1_0. No interrupts (errata)
#define PIN_GPIO39        39  // GPIO39 | Unused | Spare (J12). Board VN. Input only, no pull-ups. ADC1_3. No interrupts (errata)
#define PIN_PUMP_ZC       34  // PUMP_ZC | Digital | RobotDyn dimmer Z-C input (interrupt). 120 zero-crosses/s at 60 Hz. Input only
#define PIN_HX711_DOUT    35  // HX711_DOUT | Communications | Scale load-cell data (future, not fitted). Input only
#define PIN_GPIO32        32  // GPIO32 | Unused | Spare (J12; flow meter / tank level / display DC). ADC1_4, touch T9
#define PIN_GPIO33        33  // GPIO33 | Unused | Spare (J12; flow meter / tank level / display RST). ADC1_5, touch T8
#define PIN_PUMP_PSM      25  // PUMP_PSM | Digital | RobotDyn dimmer PSM/gate output. Pulse-skip control. 10k pull-down
#define PIN_HEATER_SSR    26  // HEATER_SSR | Digital | Boiler heater SSR (via thermal fuses). 10k pull-down
#define PIN_VALVE_SSR     27  // VALVE_SSR | Digital | 3-way solenoid valve SSR. 10k pull-down
#define PIN_STEAM_LIGHT   14  // STEAM_LIGHT | Digital | Steam temperature light relay. Pulses at boot (harmless click/flicker)
#define PIN_GPIO12        12  // GPIO12 | Unused | Spare, avoid. Strapping (MTDI): must be LOW at reset. ADC2_5
#define PIN_COFFEE_LIGHT  13  // COFFEE_LIGHT | Digital | Coffee temperature light relay
// #define PIN_GPIO9     9  // FLASH_D2 | Communications | Board SD2. Internal SPI flash - do not use
// #define PIN_GPIO10   10  // FLASH_D3 | Communications | Board SD3. Internal SPI flash - do not use
// #define PIN_GPIO11   11  // FLASH_CMD | Communications | Board CMD. Internal SPI flash - do not use
//                          (then 5V)

// ---- Right header (top to bottom): GND, then -------------------------------
#define PIN_SPI_MOSI      23  // SPI_MOSI | Unused | Spare SPI port J13 MOSI (VSPI, via 33R). Attached to VSPI (idles low); no device uses it yet
#define PIN_I2C_SCL       22  // I2C_SCL | Communications | I2C bus: ADS1115 pressure ADC, OLED, tank sensor
#define PIN_UART0_TX       1  // UART0_TX | Communications | Board TX0. USB serial / programming
#define PIN_UART0_RX       3  // UART0_RX | Communications | Board RX0. USB serial / programming
#define PIN_I2C_SDA       21  // I2C_SDA | Communications | I2C bus: ADS1115 pressure ADC, OLED, tank sensor
#define PIN_SPI_MISO      19  // SPI_MISO | Communications | MAX31855 SO, boiler thermocouple (VSPI MISO). Also SPI port J13 MISO
#define PIN_SPI_SCK       18  // SPI_SCK | Communications | MAX31855 SCK, boiler thermocouple (VSPI CLK). Also SPI port J13 SCK (via 33R)
#define PIN_TC_CS          5  // TC_CS | Communications | MAX31855 chip select, boiler thermocouple. Strapping: HIGH at reset (CS idles high)
#define PIN_STEAM_SW      17  // STEAM_SW | Digital | Steam switch, 3.3 V = on. Internal pull-down
#define PIN_COFFEE_SW     16  // COFFEE_SW | Digital | Coffee switch, 3.3 V = on. Internal pull-down
#define PIN_HX711_SCK      4  // HX711_SCK | Communications | Scale load-cell clock (future, not fitted)
#define PIN_GPIO0          0  // GPIO0 | Unused | Spare, avoid. BOOT button. Strapping: LOW at reset = download mode
#define PIN_STATUS_LED     2  // STATUS_LED | Digital | On-board LED. Strapping: LOW/float at reset
#define PIN_SPI_CS        15  // SPI_CS | Unused | Spare SPI port J13 CS, 10k pull-up. Strapping (MTDO): HIGH at reset. Not used by firmware yet
// #define PIN_GPIO8     8  // FLASH_D1 | Communications | Board SD1. Internal SPI flash - do not use
// #define PIN_GPIO7     7  // FLASH_D0 | Communications | Board SD0. Internal SPI flash - do not use
// #define PIN_GPIO6     6  // FLASH_CLK | Communications | Board CLK. Internal SPI flash - do not use

// ---- ESP32 chip pins not brought out on the WROOM-32U module ---------------
// #define PIN_GPIO37   37  // GPIO37 | Unused | Not on WROOM module (SENSOR_CAPP)
// #define PIN_GPIO38   38  // GPIO38 | Unused | Not on WROOM module (SENSOR_CAPN)
